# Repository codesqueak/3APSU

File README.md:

# Nascom 3A PSU

Nascom 3A PSU replica

## Introduction

This board is a form, fit and function replacement for the original Nascom 3A PSU.
Many of these boards are now showing their age and this is the perfect replacement for those wanting the original hardware.

Kicad View

Front PCB

Back PCB

Built PCB

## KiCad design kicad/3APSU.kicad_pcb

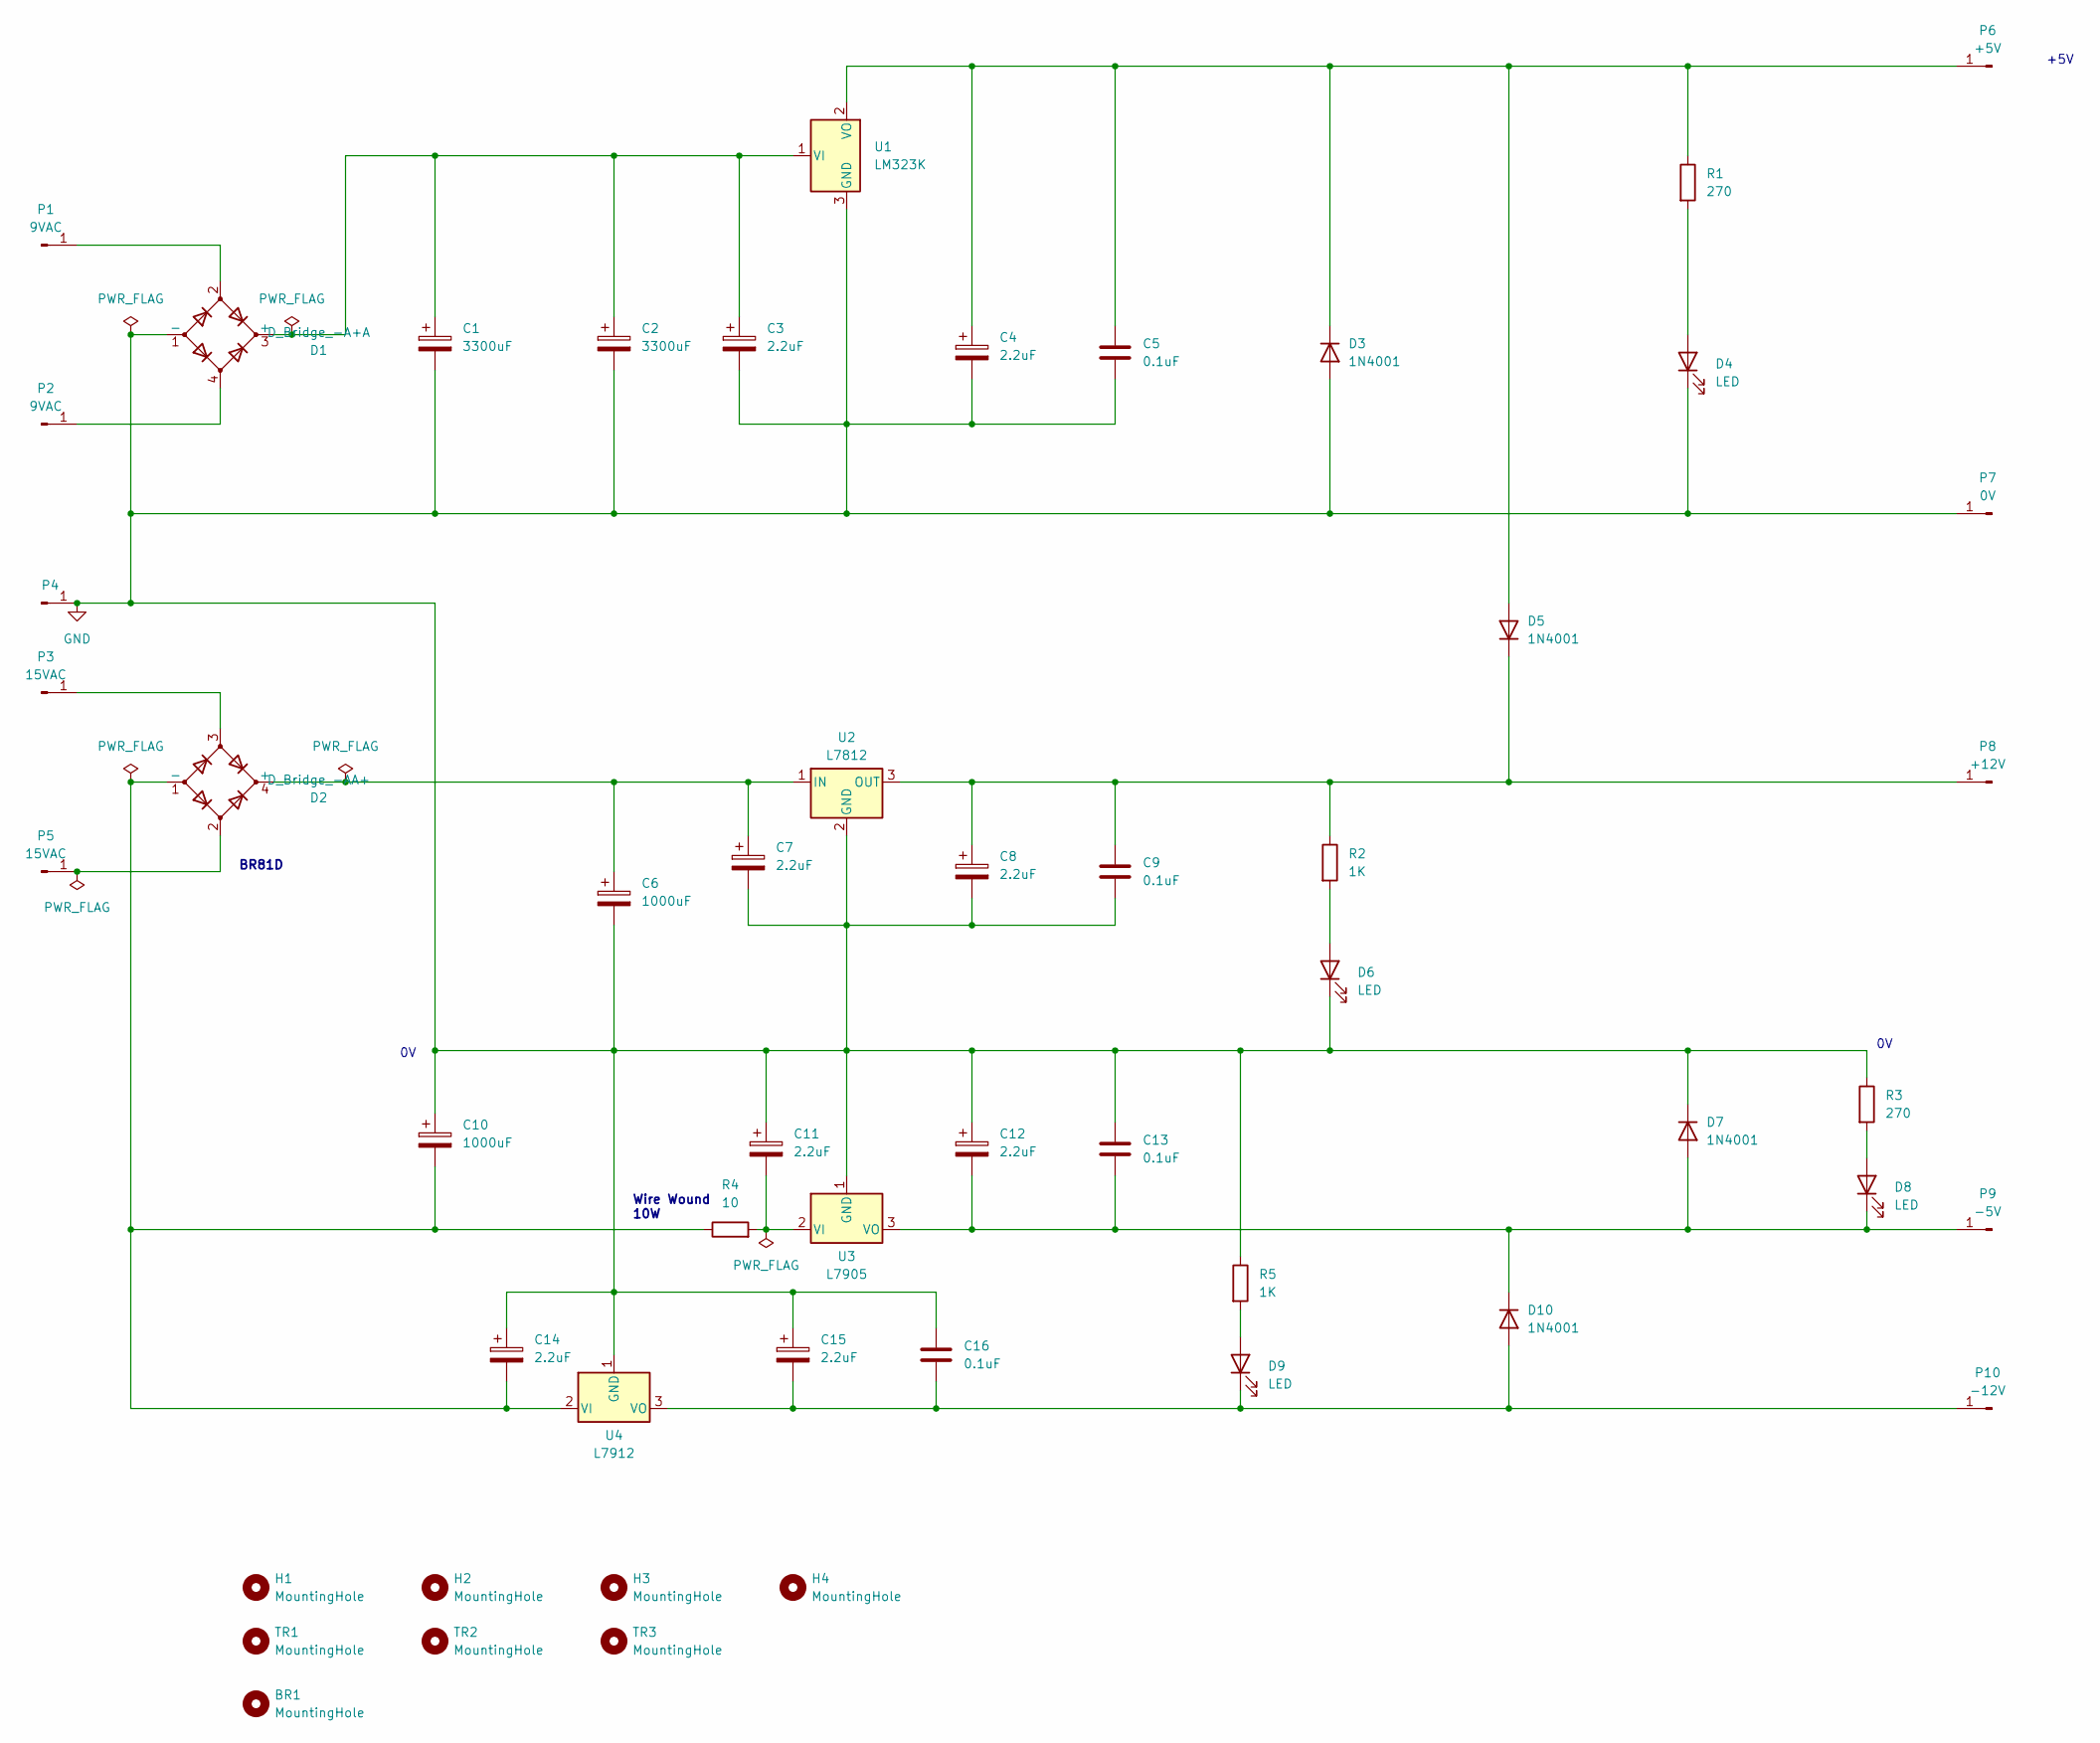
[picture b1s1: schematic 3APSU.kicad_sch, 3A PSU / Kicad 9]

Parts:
BR1: MountingHole; MountingHole_3.5mm
C1, C2: 3300uF; CP_Axial_L46.0mm_D20.0mm_P52.00mm_Horizontal
C3, C4, C7, C8, C11, C12: 2.2uF; CP_Radial_Tantal_D7.0mm_P5.00mm
C5, C9, C13, C16: 0.1uF; C_Disc_D9.0mm_W3.0mm_P6.00mm
C6, C10: 1000uF; CP_Axial_L34.5mm_D20.0mm_P41.00mm_Horizontal
C14, C15: 2.2uF; CP_Radial_Tantal_D8.0mm_P6.00mm
D1: D_Bridge_-A+A; Diode_Bridge_15.2x15.2x6.3mm_P10.9mm
D2: D_Bridge_-AA+; Bridge_Rectifier_BR81D
D3, D5, D7, D10: 1N4001; D_DO-41_SOD81_P12.70mm_Horizontal
D4, D6, D8, D9: LED; LED_D5.0mm
H1, H2, H3, H4: MountingHole; MountingHole_3.5mm
P1, P2: 9VAC; TestPoint_THTPad_D3.0mm_Drill1.5mm
P3, P5: 15VAC; TestPoint_THTPad_D3.0mm_Drill1.5mm
P4: GND; TestPoint_THTPad_D3.0mm_Drill1.5mm
P6: +5V; TestPoint_THTPad_D3.0mm_Drill1.5mm
P7: 0V; TestPoint_THTPad_D3.0mm_Drill1.5mm
P8: +12V; TestPoint_THTPad_D3.0mm_Drill1.5mm
P9: -5V; TestPoint_THTPad_D3.0mm_Drill1.5mm
P10: -12V; TestPoint_THTPad_D3.0mm_Drill1.5mm
R1, R3: 270; R_Axial_DIN0207_L6.3mm_D2.5mm_P14mm_Horizontal
R2: 1K; R_Axial_DIN0207_L6.3mm_D2.5mm_P14mm_Horizontal
R4: 10; R_Axial_Power_L31.0mm_W8.0mm_P36mm
R5: 1K; R_Axial_DIN0207_L6.3mm_D2.5mm_P15.24mm_Horizontal
TR1, TR2, TR3: MountingHole; MountingHole_3.5mm
U1: LM323K; TO-3
U2: L7812; TO-220-3_Horizontal_TabDown_staggered
U3: L7905; TO-220-3_Horizontal_TabDown_staggered
U4: L7912; TO-220-3_Horizontal_TabDown_staggered

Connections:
GND: C1.2, C2.2, C3.2, C4.2, C5.2, C6.2, C7.2, C8.2, C9.2, C10.1, C11.1, C12.1, C13.1, C14.1, C15.1, C16.1, D1.1 (-), D3.2 (A), D4.1 (K), D6.1 (K), D7.1 (K), P4.1, P7.1, R3.1, R5.1, U1.3 (GND), U2.2 (GND), U3.1 (GND), U4.1 (GND)
unnamed: C1.1, C2.1, C3.1, D1.3 (+), U1.1 (VI)
unnamed: C6.1, C7.1, D2.4 (+), U2.1 (IN)
unnamed: C10.2, C14.2, D2.1 (-), R4.1, U4.2 (VI)
unnamed: C4.1, C5.1, D3.1 (K), D5.2 (A), P6.1, R1.1, U1.2 (VO)
unnamed: D4.2 (A), R1.2
unnamed: C8.1, C9.1, D5.1 (K), P8.1, R2.1, U2.3 (OUT)
unnamed: D6.2 (A), R2.2
unnamed: D8.2 (A), R3.2
unnamed: D9.2 (A), R5.2
unnamed: C15.2, C16.2, D9.1 (K), D10.2 (A), P10.1, U4.3 (VO)
unnamed: C12.2, C13.2, D7.2 (A), D8.1 (K), D10.1 (K), P9.1, U3.3 (VO)
unnamed: D1.2, P1.1
unnamed: D1.4, P2.1
unnamed: D2.3, P3.1
unnamed: D2.2, P5.1
unnamed: C11.2, R4.2, U3.2 (VI)

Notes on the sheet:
Wire Wound 10W
+5V
BR81D

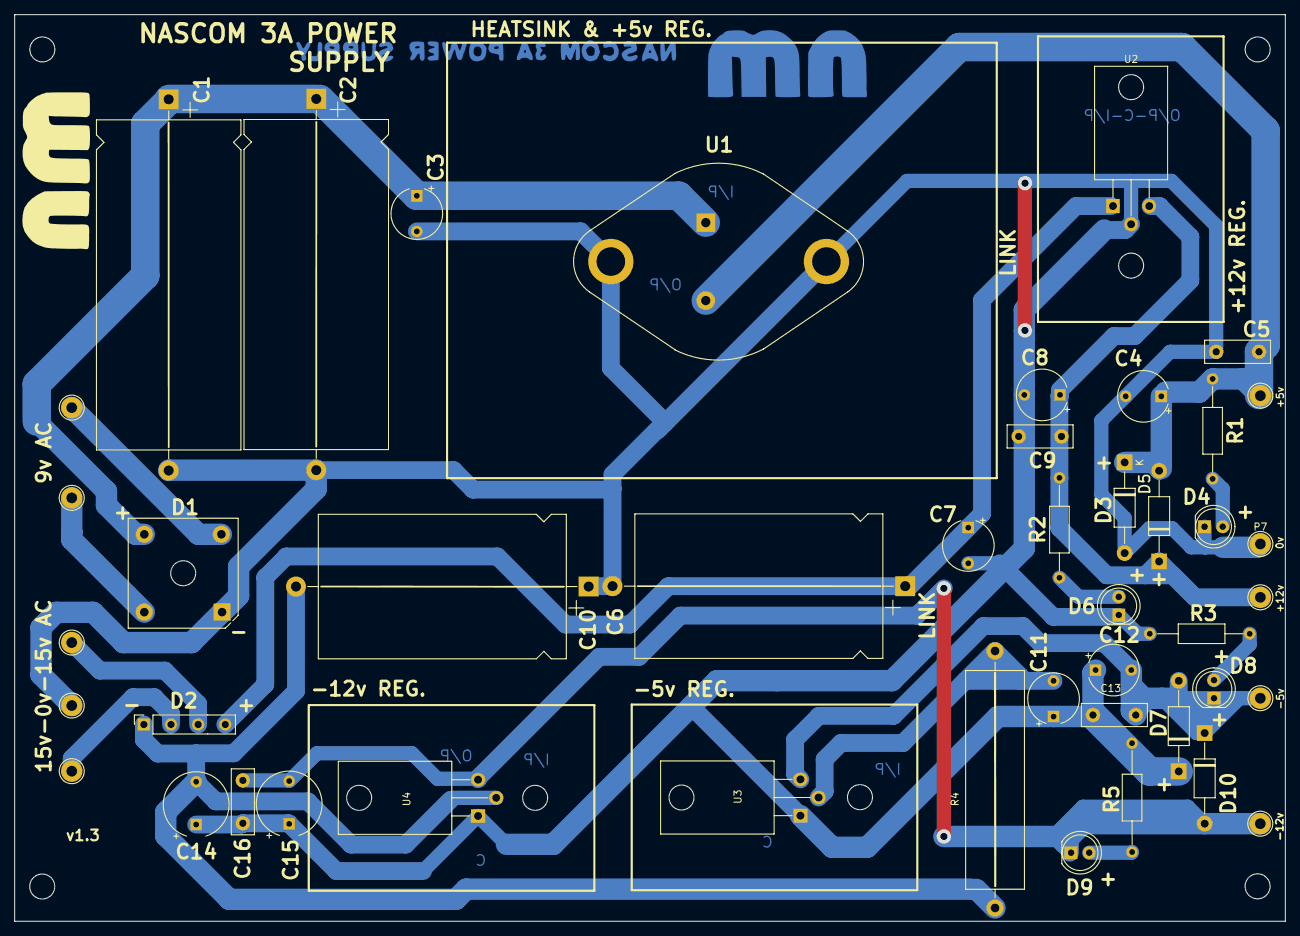
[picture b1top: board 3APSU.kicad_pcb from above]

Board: 2 copper layers, 178.0 x 127.0 mm, 55 parts (0 on the bottom side), 17 nets.

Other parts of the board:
G001: LOGO; nm logo
G002: LOGO; psu long logo inverted back copper

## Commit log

2024-07-21 First upload
2024-07-21 Update docs
2024-07-22 Tweak docs
2024-07-22 Update ToC
2025-03-29 Kicad 9 update
2025-04-06 Add code
